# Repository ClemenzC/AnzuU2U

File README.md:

# AnzuU2U
---
## Brief:

A Futaba Anzu themed USB2.0 to UART convertor with integrated CH340N chip and two LED indicators which twinkles when the device communicates with another one. With USB 2.0 defferential signal getting into CH340N,the convertor core will convert the signal to serial port signal.

You can get the [Anzu silkscreen file](/usb2uart/FutabaAnzu_Library.pretty/Futaba_Anzu.kicad_mod) and another [15*15 (mm2) version](/usb2uart/FutabaAnzu_Library.pretty/Futaba_Anzu_1515.kicad_mod) in the same folder.

---

## Key Reminder:

1. Crossing Connection:

**TX(dev_A) must be connected with RX(dev_B) and RX(dev_A) must be connected with TX(dev_B) as well otherwise signal cannot be received.**

2. Data Format:

Serial digital signals are high voltage when available. with start bit pulled low, then it started transferring data bit, check bit and halt bit respectively in order of bit sequence.

---

## Solution Features:

1. Simplified Peripherals

2. Macro Package

3. Full Speed Compatibility

4. Wide Voltage Range

5. High Baud rate

6. Plug and Play

---

## About
- Visit my [Github](https://github.com/Clemenz) <---click here.
- Go to [MyPersionBlog](https://fanhcloud.uk) to see more silkscreens.
- Futaba Anzu [Drawing](/Image/IMG_20261004_184027.png).<br>.

<div align="center" style="color: pink !important;">Love you forever Anzu!!!<3</div>

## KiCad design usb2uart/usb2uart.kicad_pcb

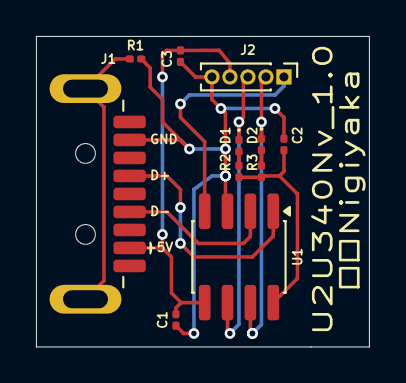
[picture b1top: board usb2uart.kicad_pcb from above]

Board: 2 copper layers, 18.5 x 17.2 mm, 12 parts (1 on the bottom side), 11 nets.

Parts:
C1, C2, C3: C; C_0201_0603Metric
D1, D2: LED; LED_0201_0603Metric
Futaba Anzu: LOGO; Futaba_Anzu_1515
J1: USB_A; USB3_A_Plug_Wuerth_692112030100_Horizontal
J2: Conn_01x05_Pin; PinHeader_1x05_P1.00mm_Vertical
R1, R2, R3: R; R_0201_0603Metric
U1: CH340N; SOP-8_3.76x4.96mm_P1.27mm

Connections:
GND: C1.2, C2.2, C3.2, J1.4 (GND), J2.5, R1.2, U1.3 (GND)
unnamed: D1.2 (A), R2.2
unnamed: D1.1 (K), J2.3, U1.6 (TXD)
unnamed: D2.2 (A), R3.2
unnamed: D2.1 (K), J2.2, U1.7 (RXD)
unnamed: J1.3 (D+), U1.1 (UD+)
unnamed: J1.2 (D-), U1.2 (UD-)
unnamed: J1.SH (Shield), R1.1
unnamed: C1.1, C3.1, J1.1 (VBUS), J2.4, U1.5 (VCC)
unnamed: J2.1, U1.4 (~RTS)
unnamed: C2.1, R2.1, R3.1, U1.8 (V3)
